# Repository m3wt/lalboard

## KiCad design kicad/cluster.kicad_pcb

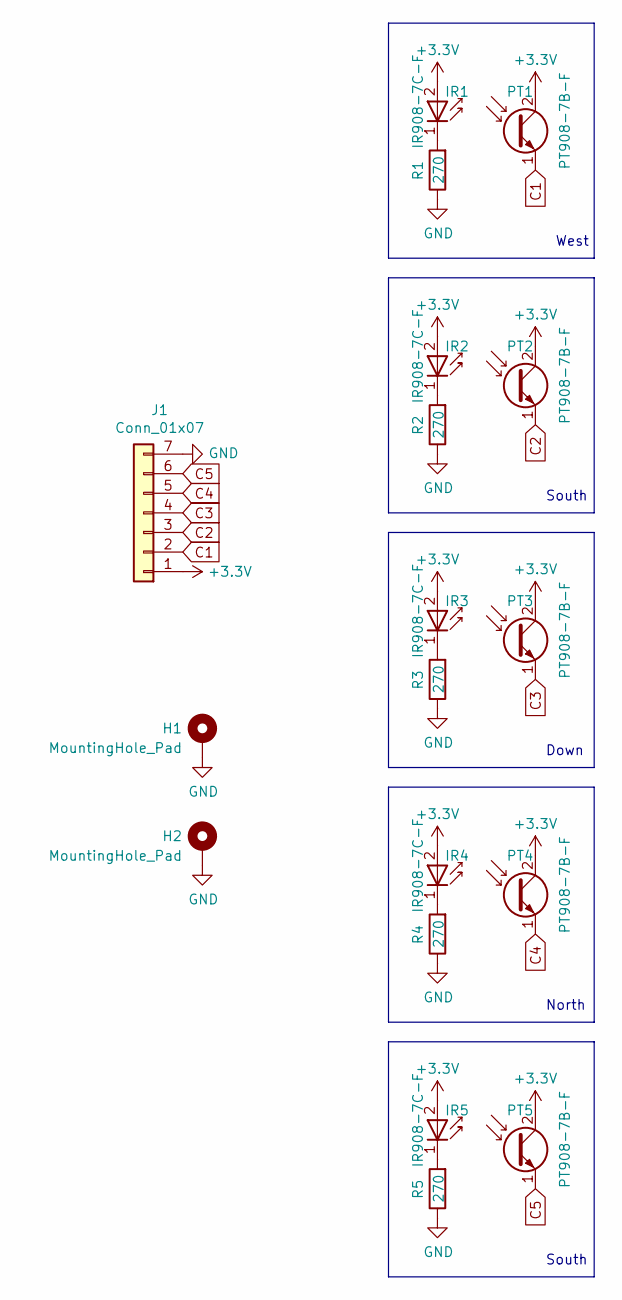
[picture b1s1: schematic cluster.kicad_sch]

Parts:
H1, H2: MountingHole_Pad; MountingHole_2.2mm_M2_DIN965_Pad
IR1, IR2, IR3, IR4, IR5: IR908-7C-F
J1: Conn_01x07; JST_ZH_S7B-ZR_1x07_P1.50mm_Horizontal
PT1, PT2, PT3, PT4, PT5: PT908-7B-F; PT908-7C-F
R1, R2, R3, R4, R5: 270; R_0805_2012Metric_Pad1.20x1.40mm_HandSolder

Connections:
+3.3V: IR1.2 (A), IR2.2 (A), IR3.2 (A), IR4.2 (A), IR5.2 (A), J1.1, PT1.2 (C), PT2.2 (C), PT3.2 (C), PT4.2 (C), PT5.2 (C)
C1: J1.2, PT1.1 (E)
C2: J1.3, PT2.1 (E)
C3: J1.4, PT3.1 (E)
C4: J1.5, PT4.1 (E)
C5: J1.6, PT5.1 (E)
GND: H1.1, H2.1, J1.7, R1.1, R2.1, R3.1, R4.1, R5.1
unnamed: IR1.1 (K), R1.2
unnamed: IR2.1 (K), R2.2
unnamed: IR3.1 (K), R3.2
unnamed: IR4.1 (K), R4.2
unnamed: IR5.1 (K), R5.2

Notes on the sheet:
Down
North
West
South

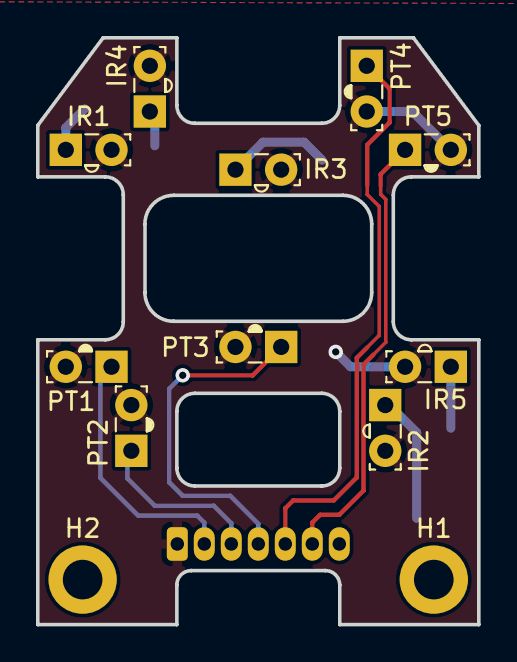
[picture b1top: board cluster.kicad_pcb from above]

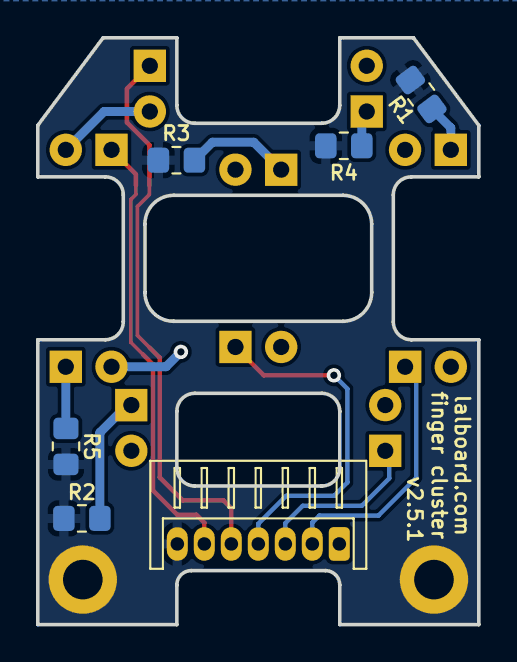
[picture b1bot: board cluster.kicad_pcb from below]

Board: 2 copper layers, 24.5 x 32.6 mm, 18 parts (6 on the bottom side), 12 nets.

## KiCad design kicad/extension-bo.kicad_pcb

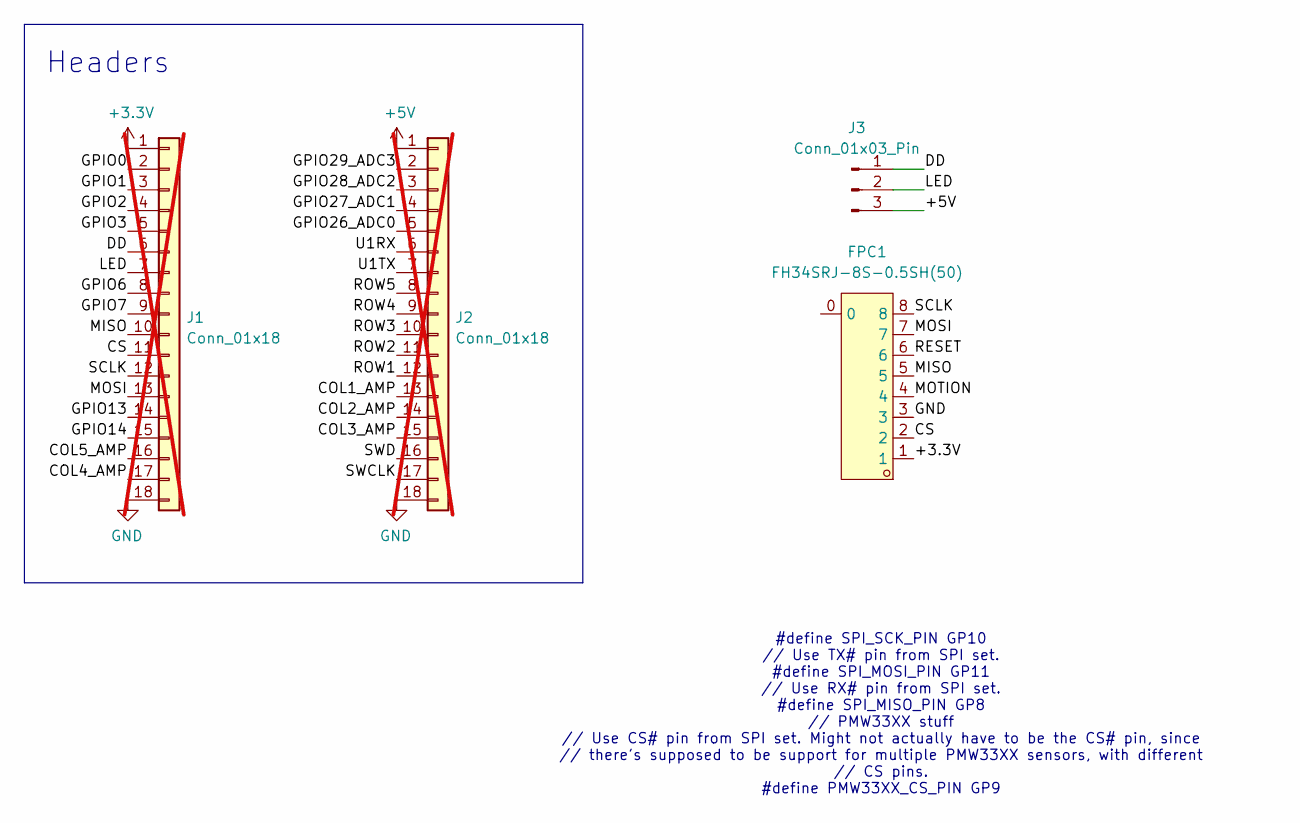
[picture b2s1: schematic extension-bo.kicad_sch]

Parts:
FPC1: FH34SRJ-8S-0.5SH(50); FPC-SMD_8P-P0.50-FH34SRJ; LCSC Part C88372
J1, J2: Conn_01x18; PinHeader_1x18_P2.54mm_Vertical; not fitted
J3: Conn_01x03_Pin; JST_ZH_B3B-ZR_1x03_P1.50mm_Vertical

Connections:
+3.3V: FPC1.1, J1.1
+5V: J2.1, J3.3
/COL1_AMP: J2.13
/COL2_AMP: J2.14
/COL3_AMP: J2.15
/COL4_AMP: J1.17
/COL5_AMP: J1.16
/CS: FPC1.2, J1.11
/DD: J1.6, J3.1
/GPIO0: J1.2
/GPIO1: J1.3
/GPIO2: J1.4
/GPIO3: J1.5
/GPIO6: J1.8
/GPIO7: J1.9
/GPIO13: J1.14
/GPIO14: J1.15
/GPIO26_ADC0: J2.5
/GPIO27_ADC1: J2.4
/GPIO28_ADC2: J2.3
/GPIO29_ADC3: J2.2
/LED: J1.7, J3.2
/MISO: FPC1.5, J1.10
/MOSI: FPC1.7, J1.13
/MOTION: FPC1.4
/RESET: FPC1.6
/ROW1: J2.12
/ROW2: J2.11
/ROW3: J2.10
/ROW4: J2.9
/ROW5: J2.8
/SCLK: FPC1.8, J1.12
/SWCLK: J2.17
/SWD: J2.16
/U1RX: J2.6
/U1TX: J2.7
GND: FPC1.3, J1.18, J2.18

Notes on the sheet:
Headers
#define SPI_SCK_PIN GP10 // Use TX# pin from SPI set. #define SPI_MOSI_PIN GP11 // Use RX# pin from SPI set. #define SPI_MISO_PIN GP8 // PMW33XX stuff // Use CS# pin from SPI set. Might not actually have to be the CS# pin, since // there's supposed to be support for multiple PMW33XX sensors, with d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

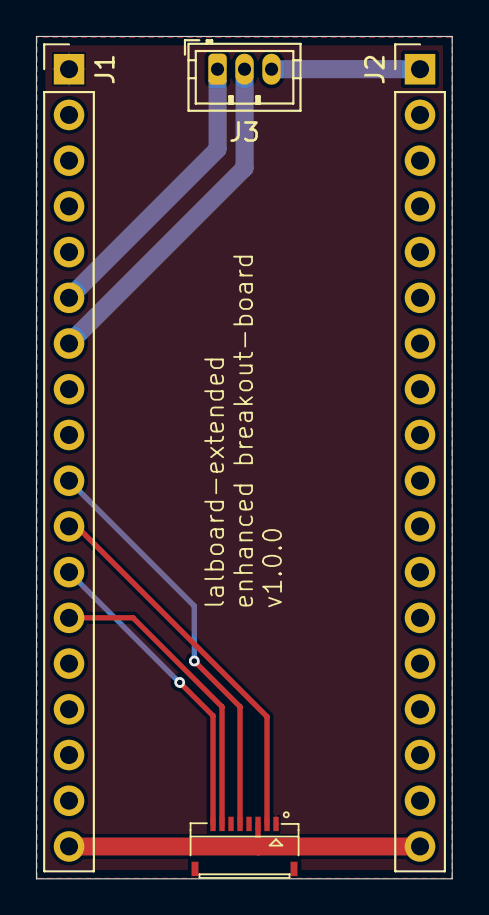
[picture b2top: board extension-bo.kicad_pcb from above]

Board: 2 copper layers, 23.1 x 46.8 mm, 4 parts (0 on the bottom side), 9 nets.

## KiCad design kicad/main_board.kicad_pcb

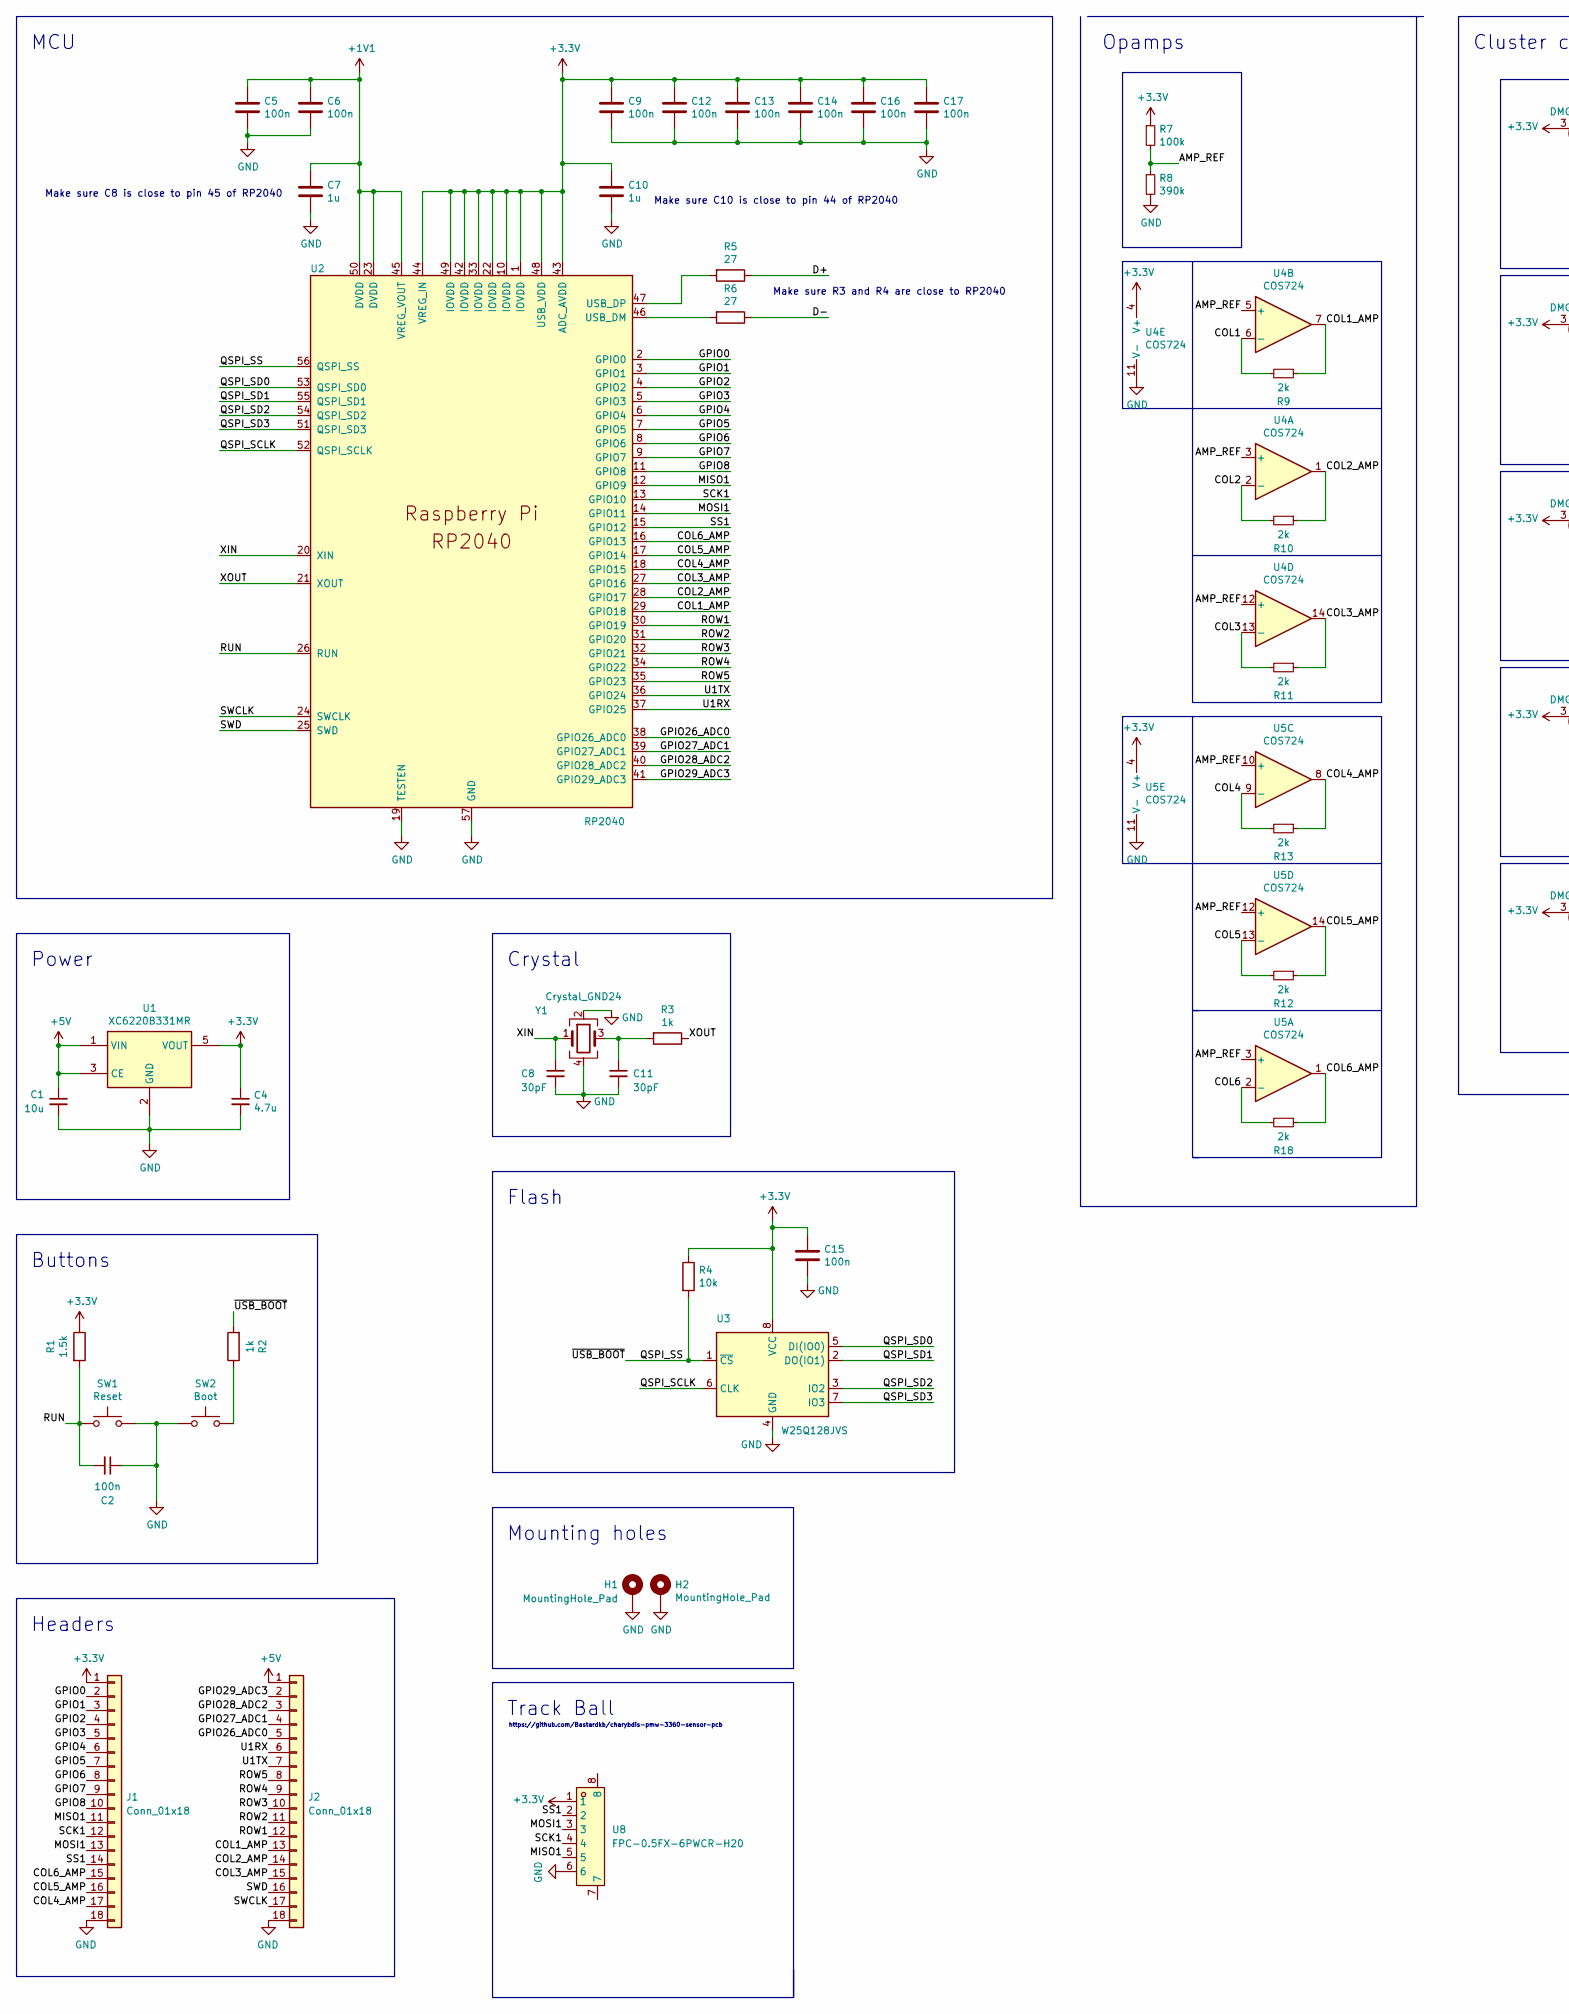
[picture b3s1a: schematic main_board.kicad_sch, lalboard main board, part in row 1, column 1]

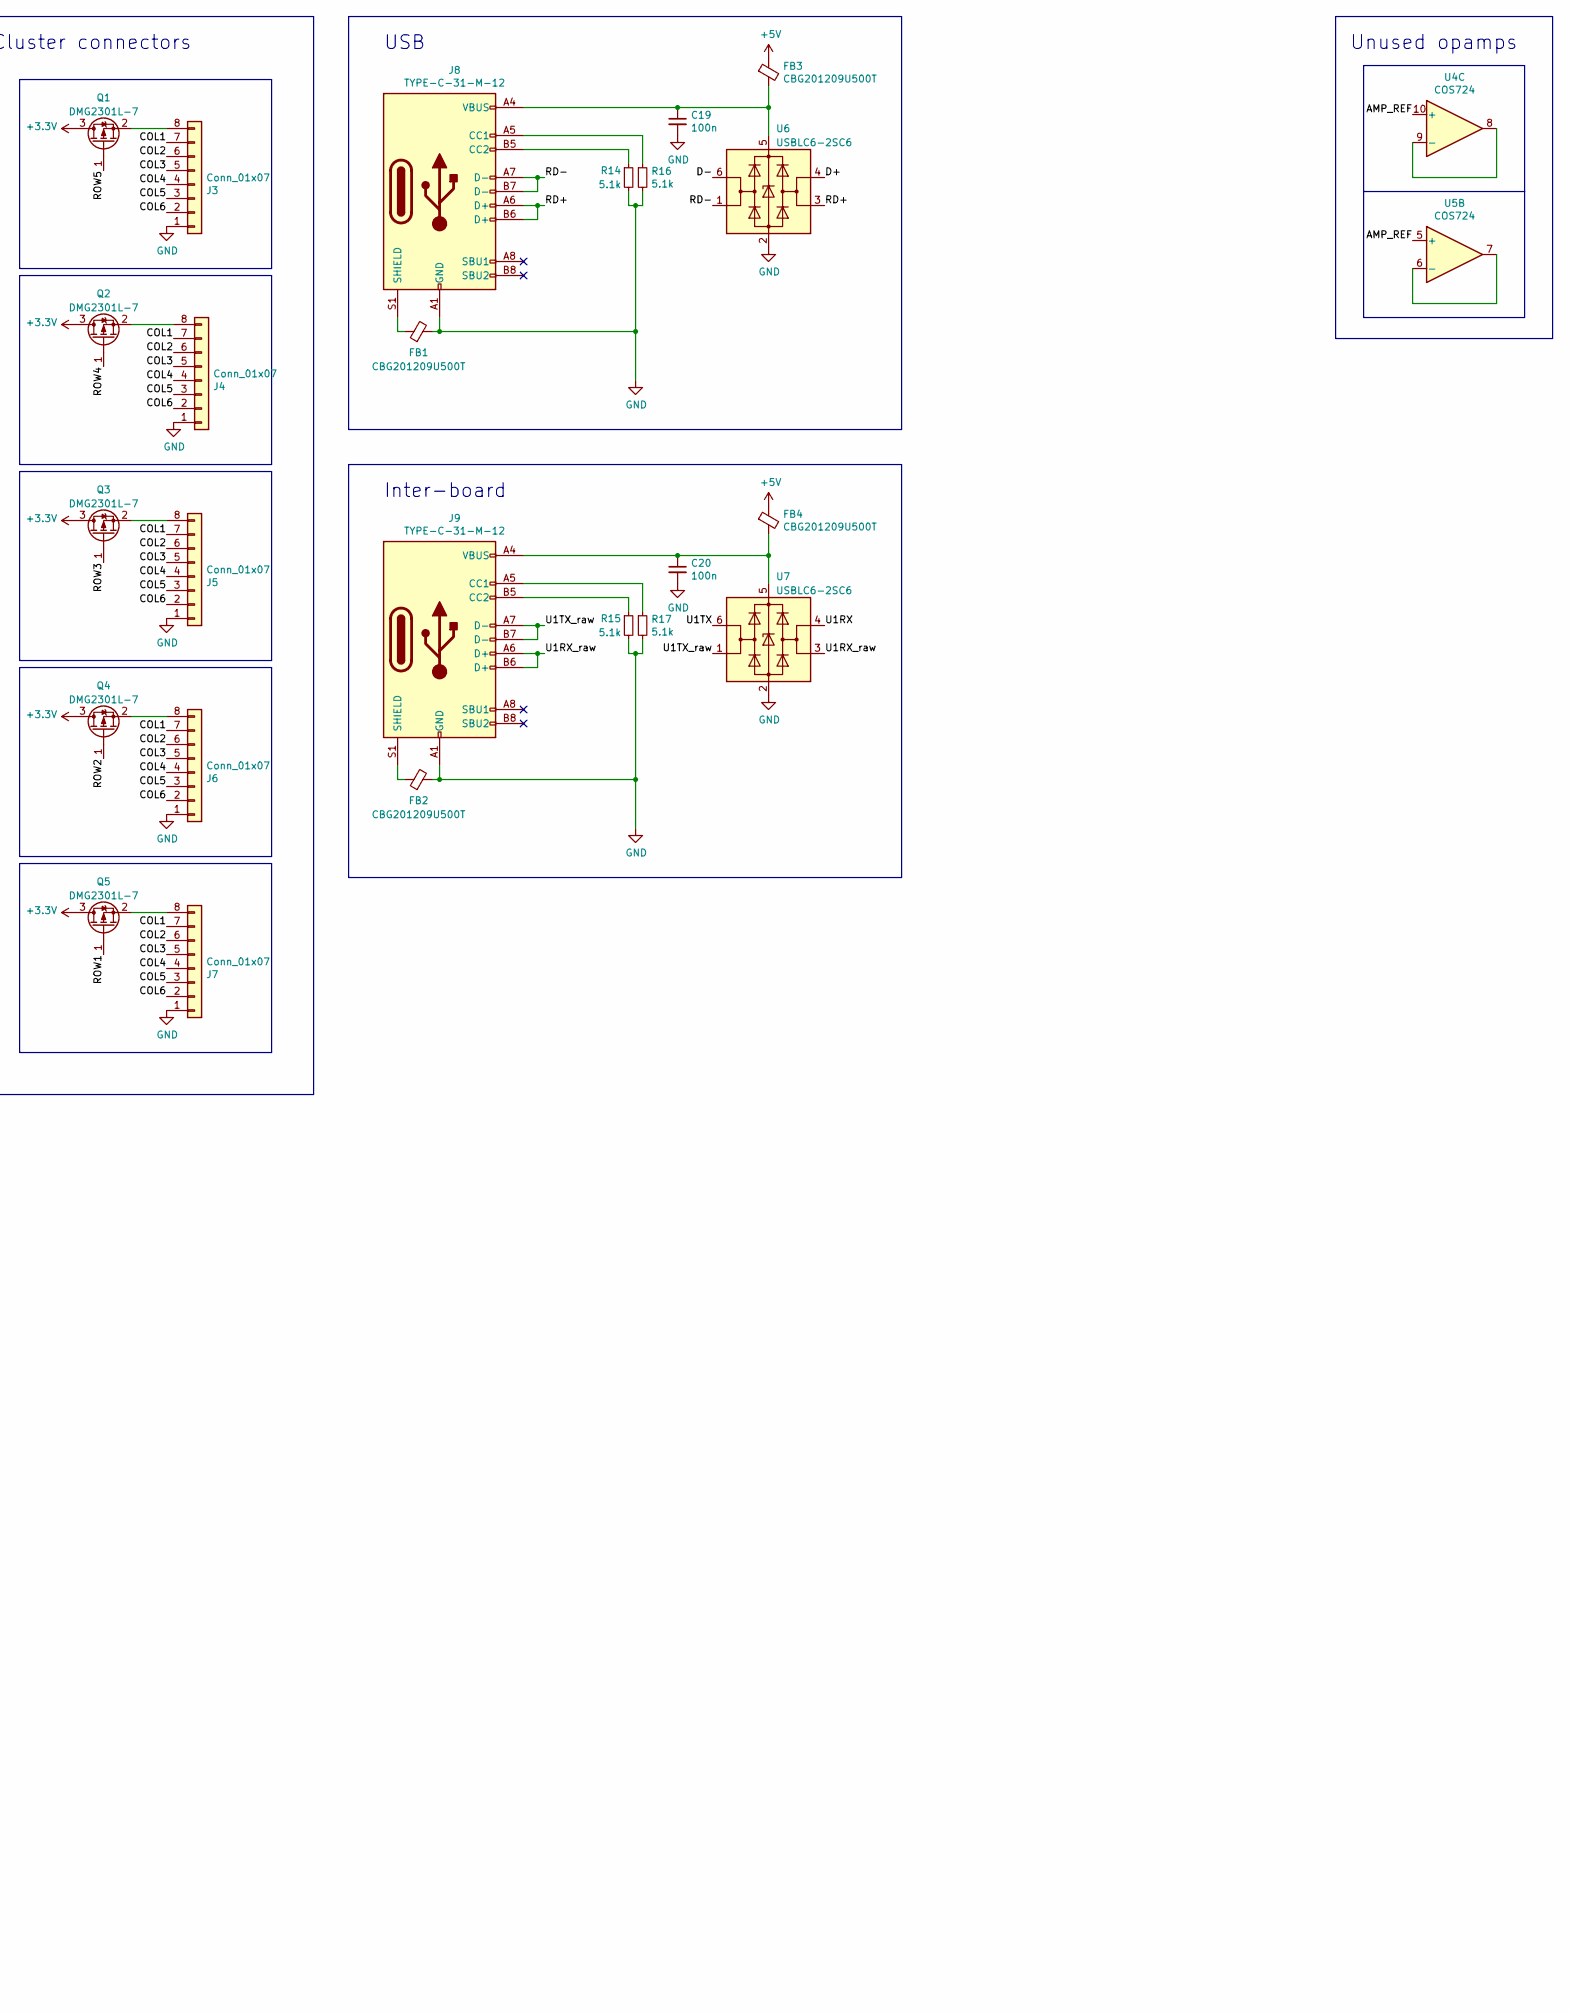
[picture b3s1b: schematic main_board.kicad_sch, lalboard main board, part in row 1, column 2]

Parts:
C1: 10u; C_0402_1005Metric; JLCPCB P/N C15525
C2, C5, C6, C9, C12, C13, C14, C15, C16, C17, C19, C20: 100n; C_0402_1005Metric; JLCPCB P/N C307331
C4: 4.7u; C_0402_1005Metric; JLCPCB P/N C23733
C7, C10: 1u; C_0402_1005Metric; JLCPCB P/N C307454
C8, C11: 30pF; C_0402_1005Metric; JLCPCB P/N C1570
FB1, FB2, FB3, FB4: CBG201209U500T; L_0805_2012Metric; JLCPCB P/N C668236
H1, H2: MountingHole_Pad; MountingHole_3.2mm_M3_DIN965_Pad
J1, J2: Conn_01x18; PinHeader_1x18_P2.54mm_Vertical
J3, J4, J5, J6, J7: Conn_01x07; FPC-SMD_8P-P0.50_AFC11-S08ICC-00
J8, J9: TYPE-C-31-M-12; USB_C_Receptacle_HRO_TYPE-C-31-M-12; JLCPCB P/N C165948
Q1, Q2, Q3, Q4, Q5: DMG2301L-7; SOT-23; JLCPCB P/N C102619
R1: 1.5k; R_0402_1005Metric; JLCPCB P/N C25867
R2, R3: 1k; C_0402_1005Metric; JLCPCB P/N C11702
R4: 10k; R_0402_1005Metric; JLCPCB P/N C25744
R5, R6: 27; C_0402_1005Metric; JLCPCB P/N C25771
R7: 100k; R_0402_1005Metric; JLCPCB P/N C25741
R8: 390k; R_0402_1005Metric; JLCPCB P/N C25782
R9, R10, R11, R12, R13, R18: 2k; R_0402_1005Metric_Pad0.72x0.64mm_HandSolder; JLCPCB P/N C4109
R14, R16, R17: 5.1k; R_0402_1005Metric; JLCPCB P/N C25905
R15: 5.1k; R_0402_1005Metric; JLCPCB C25905
SW1: Reset; SW_TS-1187A-B-A-B; JLCPCB P/N C318884
SW2: Boot; SW_TS-1187A-B-A-B; JLCPCB P/N C318884
U1: XC6220B331MR; SOT-23-5; JLCPCB P/N C3040644
U2: RP2040; RP2040-QFN-56; JLCPCB P/N C2040
U3: W25Q128JVS; SOIC-8_5.23x5.23mm_P1.27mm; JLCPCB P/N C97521
U4, U5: COS724; TSSOP-14_4.4x5mm_P0.65mm; JLCPCB P/N C2685541
U6, U7: USBLC6-2SC6; SOT-23-6; JLCPCB P/N C7519
U8: FPC-0.5FX-6PWCR-H20; FPC-SMD_6P-P0.50_FPC-0.5FX-6PWCR-H20; LCSC Part C19268261
Y1: Crystal_GND24; OSC_X322516MLB4SI; JLCPCB P/N C9002

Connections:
+1V1: C5.1, C6.1, C7.1, U2.23 (DVDD), U2.45 (VREG_VOUT), U2.50 (DVDD)
+3.3V: C4.1, C9.1, C10.1, C12.1, C13.1, C14.1, C15.1, C16.1, C17.1, J1.1, Q1.3 (D), Q2.3 (D), Q3.3 (D), Q4.3 (D), Q5.3 (D), R1.1, R4.1, R7.1, U1.5 (VOUT), U2.1 (IOVDD), U2.10 (IOVDD), U2.22 (IOVDD), U2.33 (IOVDD), U2.42 (IOVDD), U2.43 (ADC_AVDD), U2.44 (VREG_IN), U2.48 (USB_VDD), U2.49 (IOVDD), U3.8 (VCC), U4.4 (V+), U5.4 (V+), U8.1
+5V: C1.1, FB3.1, FB4.1, J2.1, U1.1 (VIN), U1.3 (CE)
/AMP_REF: R7.2, R8.1, U4.3 (+), U4.5 (+), U4.10 (+), U4.12 (+), U5.3 (+), U5.5 (+), U5.10 (+), U5.12 (+)
/COL1: J3.7, J4.7, J5.7, J6.7, J7.7, R9.2, U4.6 (-)
/COL1_AMP: J2.13, R9.1, U2.29 (GPIO18), U4.7
/COL2: J3.6, J4.6, J5.6, J6.6, J7.6, R10.2, U4.2 (-)
/COL2_AMP: J2.14, R10.1, U2.28 (GPIO17), U4.1
/COL3: J3.5, J4.5, J5.5, J6.5, J7.5, R11.2, U4.13 (-)
/COL3_AMP: J2.15, R11.1, U2.27 (GPIO16), U4.14
/COL4: J3.4, J4.4, J5.4, J6.4, J7.4, R13.2, U5.9 (-)
/COL4_AMP: J1.17, R13.1, U2.18 (GPIO15), U5.8
/COL5: J3.3, J4.3, J5.3, J6.3, J7.3, R12.2, U5.13 (-)
/COL5_AMP: J1.16, R12.1, U2.17 (GPIO14), U5.14
/COL6: J3.2, J4.2, J5.2, J6.2, J7.2, R18.2, U5.2 (-)
/COL6_AMP: J1.15, R18.1, U2.16 (GPIO13), U5.1
/D+: R5.1, U6.4 (I/O2)
/D-: R6.1, U6.6 (I/O1)
/GPIO0: J1.2, U2.2 (GPIO0)
/GPIO1: J1.3, U2.3 (GPIO1)
/GPIO2: J1.4, U2.4 (GPIO2)
/GPIO3: J1.5, U2.5 (GPIO3)
/GPIO4: J1.6, U2.6 (GPIO4)
/GPIO5: J1.7, U2.7 (GPIO5)
/GPIO6: J1.8, U2.8 (GPIO6)
/GPIO7: J1.9, U2.9 (GPIO7)
/GPIO8: J1.10, U2.11 (GPIO8)
/GPIO26_ADC0: J2.5, U2.38 (GPIO26_ADC0)
/GPIO27_ADC1: J2.4, U2.39 (GPIO27_ADC1)
/GPIO28_ADC2: J2.3, U2.40 (GPIO28_ADC2)
/GPIO29_ADC3: J2.2, U2.41 (GPIO29_ADC3)
/MISO1: J1.11, U2.12 (GPIO9), U8.5
/MOSI1: J1.13, U2.14 (GPIO11), U8.3
/QSPI_SCLK: U2.52 (QSPI_SCLK), U3.6 (CLK)
/QSPI_SD0: U2.53 (QSPI_SD0), U3.5 (DI(IO0))
/QSPI_SD1: U2.55 (QSPI_SD1), U3.2 (DO(IO1))
/QSPI_SD2: U2.54 (QSPI_SD2), U3.3 (IO2)
/QSPI_SD3: U2.51 (QSPI_SD3), U3.7 (IO3)
/QSPI_SS: R2.2, R4.2, U2.56 (QSPI_SS), U3.1 (~CS)
/RD+: J8.A6 (D+), J8.B6 (D+), U6.3 (I/O2)
/RD-: J8.A7 (D-), J8.B7 (D-), U6.1 (I/O1)
/ROW1: J2.12, Q5.1 (G), U2.30 (GPIO19)
/ROW2: J2.11, Q4.1 (G), U2.31 (GPIO20)
/ROW3: J2.10, Q3.1 (G), U2.32 (GPIO21)
/ROW4: J2.9, Q2.1 (G), U2.34 (GPIO22)
/ROW5: J2.8, Q1.1 (G), U2.35 (GPIO23)
/RUN: C2.2, R1.2, SW1.1, U2.26 (RUN)
/SCK1: J1.12, U2.13 (GPIO10), U8.4
/SS1: J1.14, U2.15 (GPIO12), U8.2
/SWCLK: J2.17, U2.24 (SWCLK)
/SWD: J2.16, U2.25 (SWD)
/U1RX: J2.6, U2.37 (GPIO25), U7.4 (I/O2)
/U1RX_raw: J9.A6 (D+), J9.B6 (D+), U7.3 (I/O2)
/U1TX: J2.7, U2.36 (GPIO24), U7.6 (I/O1)
/U1TX_raw: J9.A7 (D-), J9.B7 (D-), U7.1 (I/O1)
/XIN: C8.1, U2.20 (XIN), Y1.1
/XOUT: R3.1, U2.21 (XOUT)
GND: C1.2, C2.1, C4.2, C5.2, C6.2, C7.2, C8.2, C9.2, C10.2, C11.2, C12.2, C13.2, C14.2, C15.2, C16.2, C17.2, C19.2, C20.2, FB1.2, FB2.2, H1.1, H2.1, J1.18, J2.18, J3.1, J4.1, J5.1, J6.1, J7.1, J8.A1 (GND), J8.A12 (GND), J8.B1 (GND), J8.B12 (GND), J9.A1 (GND), J9.A12 (GND), J9.B1 (GND), J9.B12 (GND), R8.2, R14.2, R15.2, R16.2, R17.2, SW1.2, SW2.2, U1.2 (GND), U2.19 (TESTEN), U2.57 (GND), U3.4 (GND), U4.11 (V-), U5.11 (V-), U6.2 (GND), U7.2 (GND), U8.6, Y1.2, Y1.4
unnamed: C11.1, R3.2, Y1.3
unnamed: J3.8, Q1.2 (S)
unnamed: J4.8, Q2.2 (S)
unnamed: J5.8, Q3.2 (S)
unnamed: J6.8, Q4.2 (S)
unnamed: J7.8, Q5.2 (S)
unnamed: J8.A5 (CC1), R16.1
unnamed: J8.B5 (CC2), R14.1
unnamed: FB1.1, J8.S1 (SHIELD)
unnamed: J9.A5 (CC1), R17.1
unnamed: J9.B5 (CC2), R15.1
unnamed: FB2.1, J9.S1 (SHIELD)
unnamed: R2.1, SW2.1
unnamed: R6.2, U2.46 (USB_DM)
unnamed: R5.2, U2.47 (USB_DP)
unnamed: U4.8, U4.9 (-)
unnamed: U5.6 (-), U5.7
unnamed: C19.1, FB3.2, J8.A4 (VBUS), J8.A9 (VBUS), J8.B4 (VBUS), J8.B9 (VBUS), U6.5 (VBUS)
unnamed: C20.1, FB4.2, J9.A4 (VBUS), J9.A9 (VBUS), J9.B4 (VBUS), J9.B9 (VBUS), U7.5 (VBUS)

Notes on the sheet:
Cluster connectors
Make sure R3 and R4 are close to RP2040
USB
Power
Headers
Buttons
Make sure C8 is close to pin 45 of RP2040
Track Ball
Opamps
Unused opamps
MCU
Inter-board
https://github.com/Bastardkb/charybdis-pmw-3360-sensor-pcb
Crystal
Mounting holes
Make sure C10 is close to pin 44 of RP2040
Flash

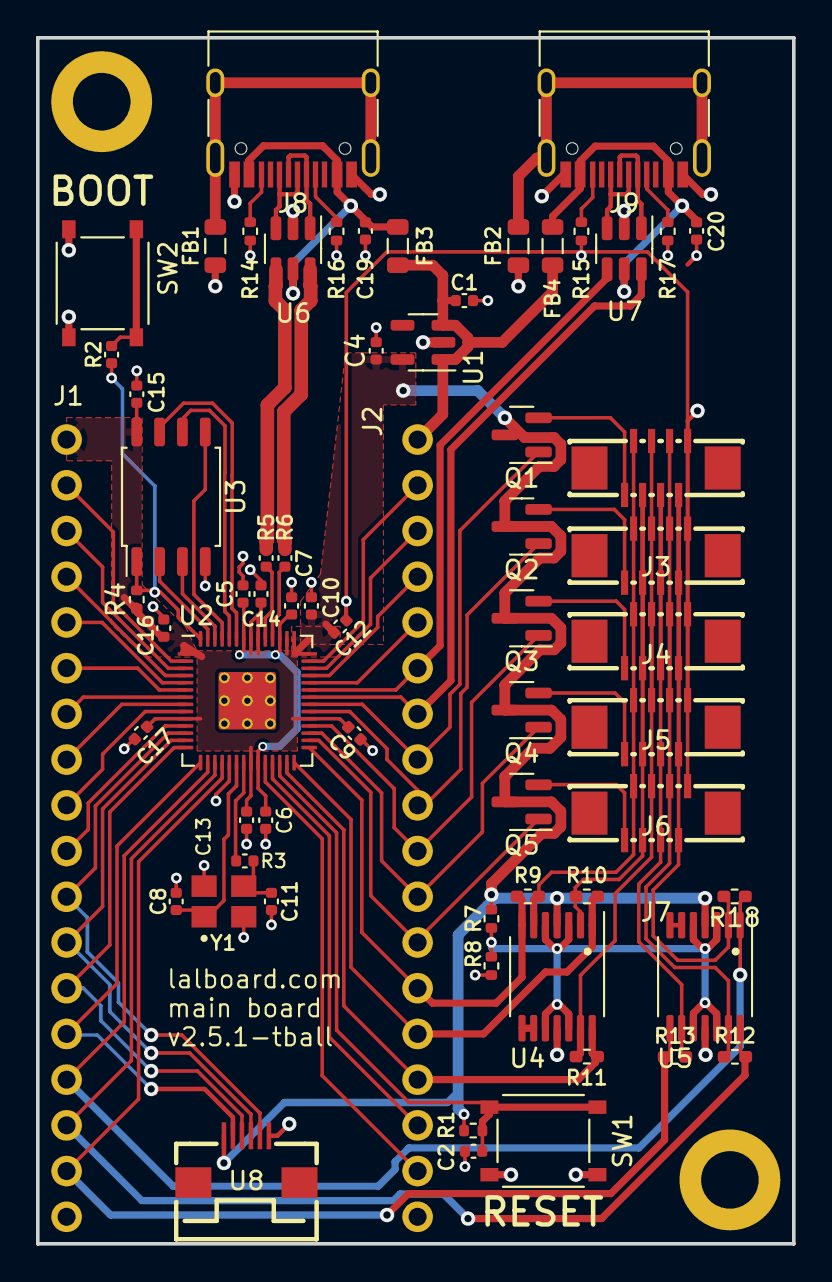
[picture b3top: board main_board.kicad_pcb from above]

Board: 2 copper layers, 42.0 x 67.0 mm, 67 parts (0 on the bottom side), 77 nets.

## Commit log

2025-04-02 Modifications to additional headers
    - Added mouse header
    - Added additional columns to support thumb through
    - Switched to ribbon cables
2025-04-02 Single Trackball Correction
    No need for two trackballs per side.
2025-04-02 DRC Fixes
    DRC Fixes
2025-07-01 Initial commit of lalboard extended features, including breakout board.
